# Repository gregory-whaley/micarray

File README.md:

# MicArray
Multichannel USB microphone for Raspbery Pi Pico for use in acoustic array beamforming.

This C code and PIO code will accept I2S data from two MEMS microphones and create a USB 2.0 audio microphone source with two channels intially, and expandable to more channels in later versions.  The target MCU is the Raspberry Pi RP2040 on the Pico board and the target microphone is the Invensense ICS-43434 MEMS microphone with I2S interface.  The code supports the following features:

- USB 2.0 device enumerates as a standard audio class 2.0 isochronous streaming device.  No host driver installation is necessary for Windows/Mac/Linux.
- Audio sample rate is fixed at 48000 Hz.
- Data is encoded as PCM samples SE_32 (32 bits per sample).
- Audio volume (gain) is fixed and so volume control must be performed at the host application level.
- MEMS microphone interface is I2S with both outputs interleaved into one data path.
- Target MEMS microphone is Invensense ICS-43434, 24 bits/sample.
- Uses Raspberry Pi Pico RP2040 development board.
- USB enumeration of HID interface providing MCU (environment) temperature and microphone separation distance which are important for acoustic beamforming calculations.

## Documentation

### Hardware
The system can be constructed using a Raspberry Pi Pico development board and two MEMS microphone evaluation boards from Adafruit (Part #6049) as shown in the following diagram.
  Connection Diagram for Dual Microphones

### Supported Boards
- Raspberry Pi Pico/W (RP2040)
- Adafruit #6049 MEMS microphone evaluation board

### Building and Installing

The code is built using the standard [Raspberry Pi Pico SDK](https://github.com/raspberrypi/pico-sdk) and leverages the [TinyUSB library](https://github.com/hathach/tinyusb) for usb functions.

Instructions for installing the Pico development SDK [can be found here](https://rptl.io/pico-get-started).

Clone this repo to a new folder in your local system.
```shell
mkdir micarray
git clone https://github.com/gregory-whaley/micarray.git
```

Unfortunately the version of TinyUSB which is automatically included with the Pico SDK has a buffer allocation error in streaming audio.  This error has been fixed in version 0.19.0, so we must instead clone the current TinyUSB repository also to a separate folder in your local system.
```shell
mkdir tinyusb
git clone https://github.com/hathach/tinyusb.git
```

  The CMakeLists.txt file in the micarray repo includes a redirection to this updated local TinyUSB folder, and so you must edit the following line to point cmake to your local TinyUSB folder.
```
set(PICO_TINYUSB_PATH "/home/YOUR_LOCAL_FOLDER/tinyusb")
```

The code is built from the linux command line as follows:
```shell
cd YOUR_LOCAL_FOLDER/micarray
mkdir build
cd build
cmake .. -DBOARD=raspberry_pi_pico
make
```
which will produce a *.uf2 binary output file in the build folder.  Then follow the standard process to flash the file to the pico by plugging in the pico with the bool_sel button pressed, and copy the uf2 file to the pico folder which is mounted to the system.  After flashing, the pico will present both a standard audio streaming USB interface, and an HID interface.  The audio function can be tested using any recording application such as Audacity.  The hid_test.py script can be used to query the HID functions which returns the pico device temperature and a (hard coded) number representing the physical distance between microphones in the array.  In linux HID devices are owned by root by default and thus blocked from user access, so the simplest method to run the python script is to run as root.

### Custom PCB
A printed circuit board was designed for this system to support two microphones at a fixed spacing which is important for beamforming use.  KiCAD PCB files are included herein.  In this case the microphone access ports are 390 mm apart.
Custom PCB of two microphone sensor

### Weather Tolerant Enclosure
A mechanical cover for this circuit board was designed and built where almost the entire board is coated in polyurethane to allow for use outdoors for long term sensing.
MicArray sensor with polyurethane coating

A 3D model was designed for the enclosure and was printed in SLS resin to serve as a form for generating a silicone mold.  The PCB is then placed in the finished mold and liquid polyurethane is poured in the mold to completely embed the PCB within the polyurethane except for the two small microphone access ports.  The microphone ports are angled at 45 degrees from vertical to ensure rainwater will not ingress into the ports.  A flat flexible USB cable was chosen to connect the microphone so that the cable may fit under a weather seal such as in a window frame or under a gasket in a sealed enclosure.  This allows the host computer to communicate with the microphones from a dry environment.

## License
The MIT License (MIT)

Copyright (C) 2025 The Whaley Group

Permission is hereby granted, free of charge, to any person obtaining a copy of this software and associated documentation files (the 'Software'), to deal in the Software without restriction, including without limitation the rights to use, copy, modify, merge, publish, distribute, sublicense, and/or sell copies of the Software, and to permit persons to whom the Software is furnished to do so, subject to the following conditions:

The above copyright notice and this permission notice shall be included in all copies or substantial portions of the Software.

THE SOFTWARE IS PROVIDED 'AS IS', WITHOUT WARRANTY OF ANY KIND, EXPRESS OR IMPLIED, INCLUDING BUT NOT LIMITED TO THE WARRANTIES OF MERCHANTABILITY, FITNESS FOR A PARTICULAR PURPOSE AND NONINFRINGEMENT. IN NO EVENT SHALL THE AUTHORS OR COPYRIGHT HOLDERS BE LIABLE FOR ANY CLAIM, DAMAGES OR OTHER LIABILITY, WHETHER IN AN ACTION OF CONTRACT, TORT OR OTHERWISE, ARISING FROM, OUT OF OR IN CONNECTION WITH THE SOFTWARE OR THE USE OR OTHER DEALINGS IN THE SOFTWARE.

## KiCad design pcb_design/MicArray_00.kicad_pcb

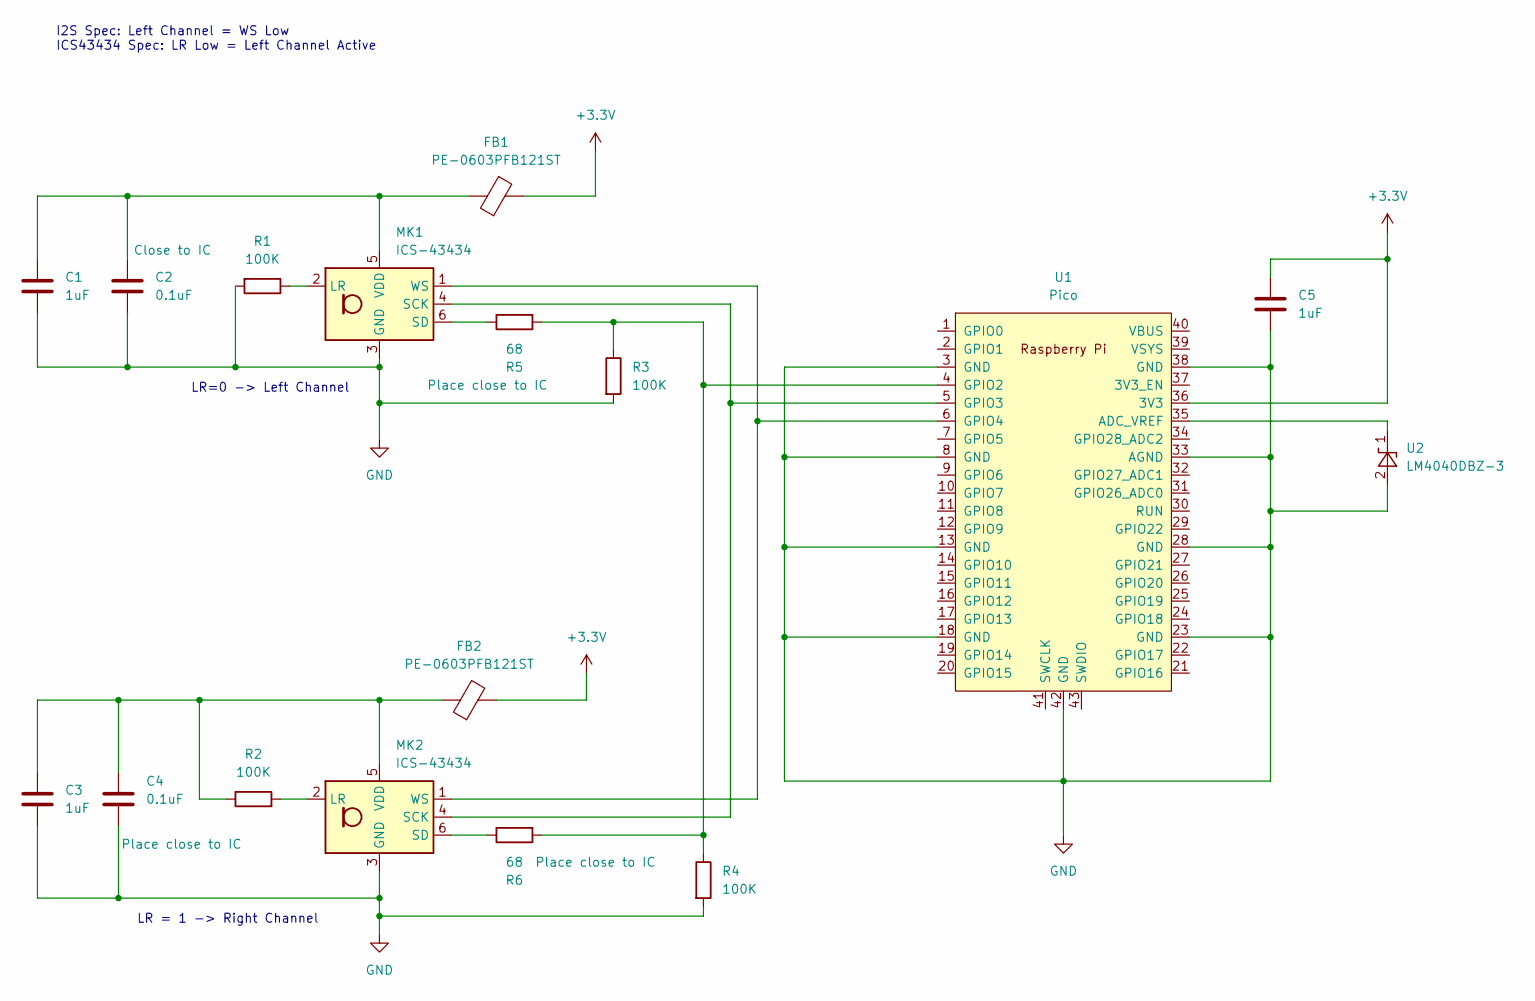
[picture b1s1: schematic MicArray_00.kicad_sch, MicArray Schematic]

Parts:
C1, C3, C5: 1uF; C_0603_1608Metric_Pad1.08x0.95mm_HandSolder
C2, C4: 0.1uF; C_0603_1608Metric_Pad1.08x0.95mm_HandSolder
FB1, FB2: PE-0603PFB121ST; C_0603_1608Metric_Pad1.08x0.95mm_HandSolder
MK1, MK2: ICS-43434; InvenSense_ICS-43434-6_3.5x2.65mm
R1, R2, R3, R4: 100K; R_0603_1608Metric_Pad0.98x0.95mm_HandSolder
R5, R6: 68; R_0603_1608Metric_Pad0.98x0.95mm_HandSolder
U1: Pico; RPi_Pico_SMD_TH
U2: LM4040DBZ-3; SOT-23

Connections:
+3.3V: C5.1, FB1.2, FB2.2, U1.36 (3V3)
GND: C1.2, C2.2, C3.2, C4.2, C5.2, MK1.3 (GND), MK2.3 (GND), R1.2, R3.2, R4.2, U1.3 (GND), U1.8 (GND), U1.13 (GND), U1.18 (GND), U1.23 (GND), U1.28 (GND), U1.33 (AGND), U1.38 (GND), U1.42 (GND), U2.2 (A)
unnamed: MK1.2 (LR), R1.1
unnamed: MK1.4 (SCK), MK2.4 (SCK), U1.5 (GPIO3)
unnamed: MK1.6 (SD), R5.1
unnamed: C1.1, C2.1, FB1.1, MK1.5 (VDD)
unnamed: MK1.1 (WS), MK2.1 (WS), U1.6 (GPIO4)
unnamed: MK2.2 (LR), R2.2
unnamed: MK2.6 (SD), R6.1
unnamed: C3.1, C4.1, FB2.1, MK2.5 (VDD), R2.1
unnamed: U1.35 (ADC_VREF), U2.1 (K)
unnamed: R3.1, R4.1, R5.2, R6.2, U1.4 (GPIO2)

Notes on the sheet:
LR = 1 -> Right Channel
LR=0 -> Left Channel
I2S Spec: Left Channel = WS Low ICS43434 Spec: LR Low = Left Channel Active

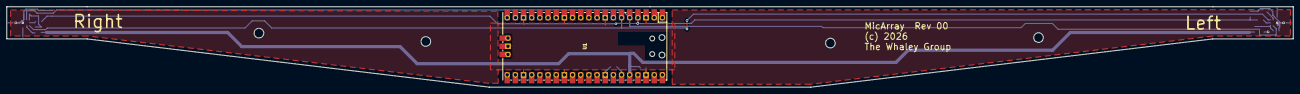
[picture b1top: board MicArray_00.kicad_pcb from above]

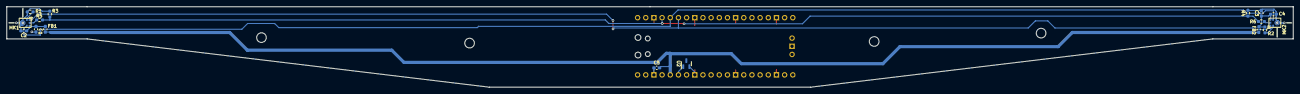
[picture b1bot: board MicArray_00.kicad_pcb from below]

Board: 2 copper layers, 400.0 x 25.0 mm, 17 parts (16 on the bottom side), 12 nets.

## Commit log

2025-12-16 commit of functioning device before HID code inserted.
2025-12-16 first compile and usb data flow verified. sample rate is offhowever.
2025-12-16 Realized no scaling of the raw data is needed.
2025-12-16 Compiles and usb device enumerates properly however fails to transfer iso samples due to EP conflict. Seems to be a TUSB bug.
2025-12-16 Removed old comments.
2025-12-16 Combined audio and hid functions and tests functional!!
2025-12-16 valid I2S data flow confirmed!
2025-12-16 data is flowing but not correct values.
2025-12-16 Added some introductory comments, the MIT license, and set the LED on the board to indicate power on.
2025-12-16 Added sending of zeros when mute is active.
2025-12-16 first successful compile of main, library, and pio
2025-12-16 runs for first time without missing or extra samples on one channel. Tinyusb driver uses no explicit flow control and has a 4X input buffer for the EP.
2025-12-16 pio should be ready to test
2025-12-16 first error free usb initialization!!
2025-12-16 compiles and enumerates without error using updated tinyusb repo. Some streaming observed for the first time!!
2025-12-16 intial commit
2025-12-17 updated USB VID and PID allocated by Raspberry Pi Foundation. Updated MIT license text.
2025-12-17 Updated readme and added connection diagram file.
2026-03-21 updated pio code to fix improper LRCLK timing. Generated new batch of firmware burn files for SN 1-5.
2026-03-21 updated descriptors for serial number string reflecting the PCB number, and updating the temperature moeasurement code in hid callback to use the 3.00V reference in the calculation, and set the mic d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
2026-03-21 Commit for release version 0.1.0 using the usb serials string to hold the firmware revision and serial number in the format "FWX.X.X-SN000X".
2026-04-13 Included electrical and mechanical design files and updated the README file.
2026-04-13 Fixed typos in README.

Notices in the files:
pcb_design/MicArray_00.kicad_pcb:
(c) 2026
